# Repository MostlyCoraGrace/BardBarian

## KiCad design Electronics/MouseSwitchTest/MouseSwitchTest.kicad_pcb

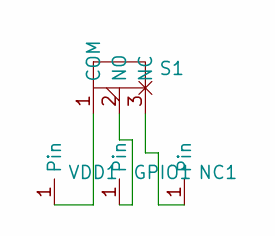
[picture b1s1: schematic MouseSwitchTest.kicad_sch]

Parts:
GPIO1: Header
NC1: Header
S1: Kailh GM 4.0 Red CMI126601D01
VDD1: Header

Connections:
unnamed: GPIO1.1, S1.2 (NO)
unnamed: NC1.1, S1.3 (NC)
unnamed: S1.1 (COM), VDD1.1

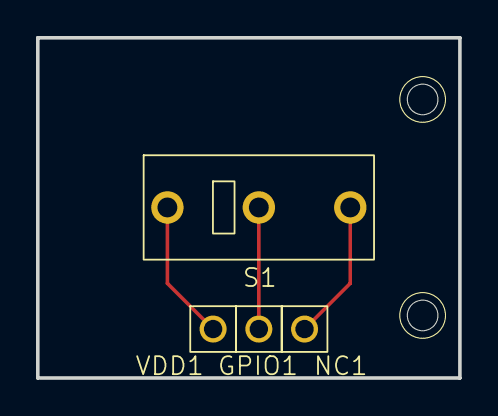
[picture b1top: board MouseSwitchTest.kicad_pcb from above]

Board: 2 copper layers, 23.5 x 18.9 mm, 4 parts (0 on the bottom side), 3 nets.

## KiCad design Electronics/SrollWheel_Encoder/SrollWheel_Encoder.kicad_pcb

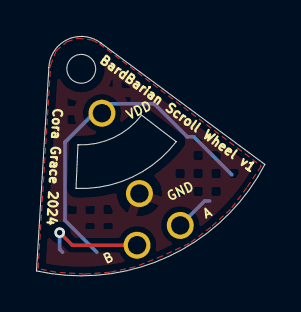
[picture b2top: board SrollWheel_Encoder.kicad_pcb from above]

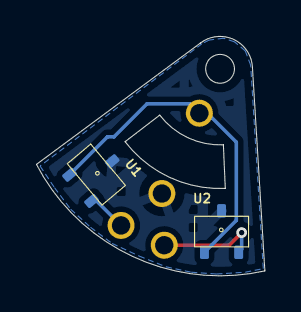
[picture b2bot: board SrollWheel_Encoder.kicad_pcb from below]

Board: 2 copper layers, 12.7 x 13.3 mm, 6 parts (2 on the bottom side), 4 nets.

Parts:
A: Header
B: Header
GND: Header
U1, U2: US5881LSE-AAA-000-RE (TSOT-3L)
VDD: Header

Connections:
/A: A.1, U1.2 (OUT)
/B: B.1, U2.2 (OUT)
/GND: GND.1, U1.3 (GND), U2.3 (GND)
/VDD: U1.1 (VDD), U2.1 (VDD), VDD.1

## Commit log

2024-03-27 fixed up some geometry
2024-03-29 added the middle click foot
2024-03-30 init kicad files
2024-03-31 started the scroll wheel pcb
2024-04-03 started work on the springs
2024-04-04 fixed the return stop of the scroll middle click hinge intersecting with the test jig
2024-04-04 moved the footprint library to its own root folder
2024-04-04 made the symbol library paths relative
2024-04-05 added kailh gm4 mouse switch footprint and symbol
2024-04-05 added the mouse switch test pcb
2024-04-05 initialised the 3d print files
2024-04-20 beveled the sensor holder
2024-04-21 updated the middle click pcb
2024-04-21 removed the old encoder pcb
2024-04-21 removed old printable files
2024-04-26 rotated the middle click mouse switch to avoid collisions with the assistive springs
2024-10-31 dont remember what i did here but something changed
